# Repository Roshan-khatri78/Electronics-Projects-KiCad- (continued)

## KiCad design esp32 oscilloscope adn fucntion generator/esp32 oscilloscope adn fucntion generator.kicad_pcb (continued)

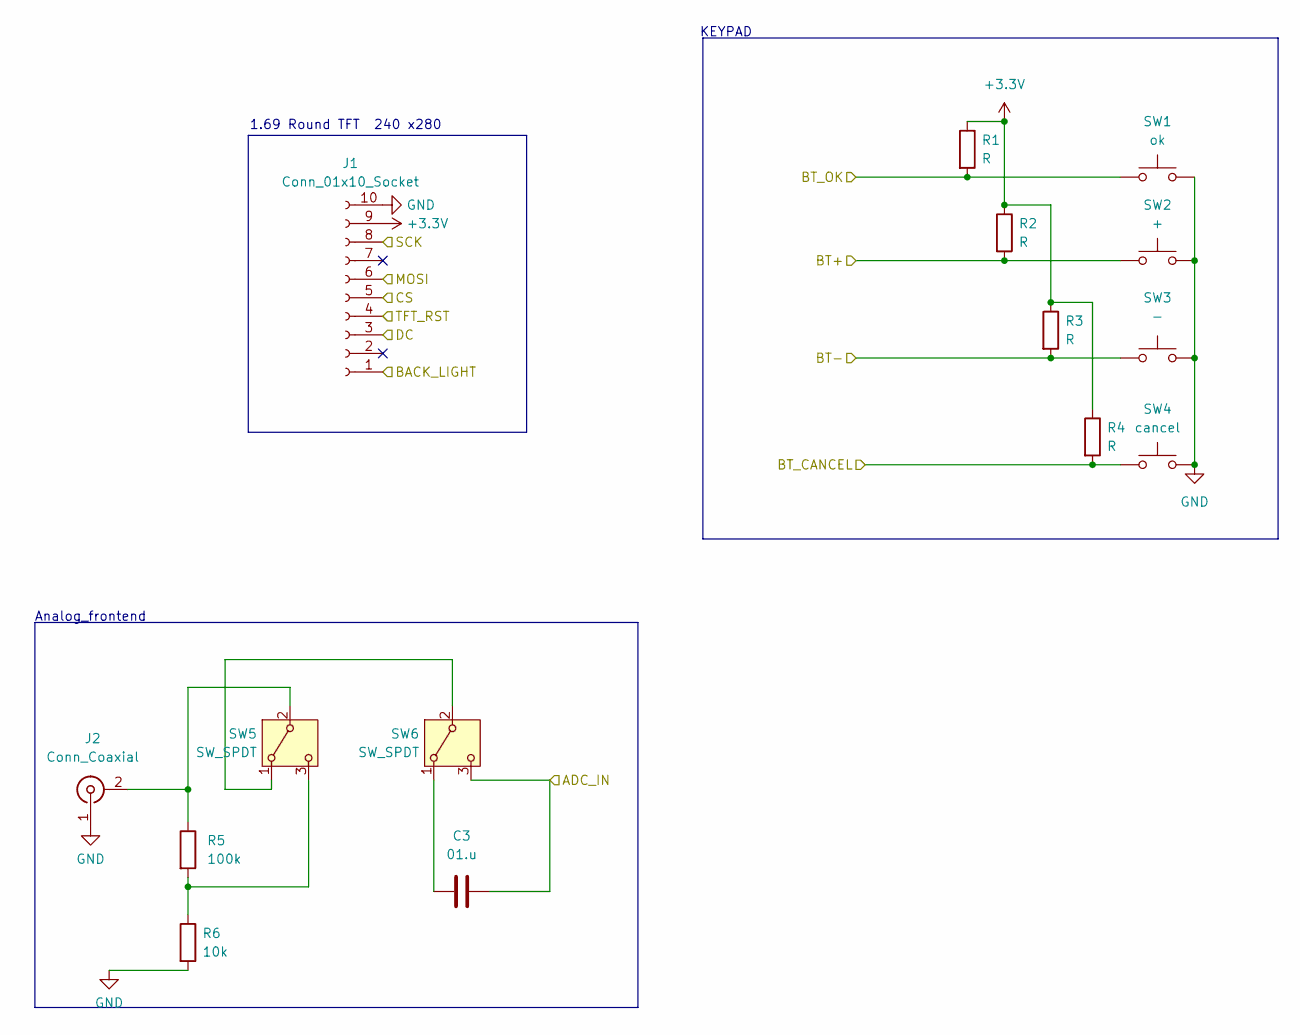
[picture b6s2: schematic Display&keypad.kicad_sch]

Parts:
C3: 01.u; C_1210_3225Metric
J1: Conn_01x10_Socket; PinSocket_1x10_P2.00mm_Vertical
J2: Conn_Coaxial; BNC_TEConnectivity_1478035_Horizontal
R1, R2, R3, R4: R; R_1210_3225Metric
R5: 100k; R_1210_3225Metric
R6: 10k; R_1210_3225Metric
SW1: ok; SW_PUSH_6mm
SW2: +; SW_PUSH_6mm
SW3: -; SW_PUSH_6mm
SW4: cancel; SW_PUSH_6mm
SW5, SW6: SW_SPDT; SW_E-Switch_EG1271_SPDT

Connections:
+3.3V: J1.9, R1.1, R2.1, R3.1, R4.1; also elsewhere on the board
/ADC_IN: C3.2, SW6.3 (C); also elsewhere on the board
/BACKLIGHT: J1.1; also elsewhere on the board
/BT+: R1.2, SW1.1; also elsewhere on the board
/BT-: R3.2, SW3.1; also elsewhere on the board
/BT_CANCEL: R4.2, SW4.1; also elsewhere on the board
/BT_OK: R2.2, SW2.1; also elsewhere on the board
/CS: J1.5; also elsewhere on the board
/DC: J1.3; also elsewhere on the board
/MOSI: J1.6; also elsewhere on the board
/SCK: J1.8; also elsewhere on the board
/TFT_RST: J1.4; also elsewhere on the board
GND: J1.10, J2.1 (In), R6.2, SW1.2, SW2.2, SW3.2, SW4.2; also elsewhere on the board
unnamed: J2.2 (Ext), R5.1, SW5.2 (B)
unnamed: SW5.1 (A), SW6.2 (B)
unnamed: R5.2, R6.1, SW5.3 (C)
unnamed: C3.1, SW6.1 (A)

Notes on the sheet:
Analog_frontend
1.69 Round TFT 240 x280
KEYPAD

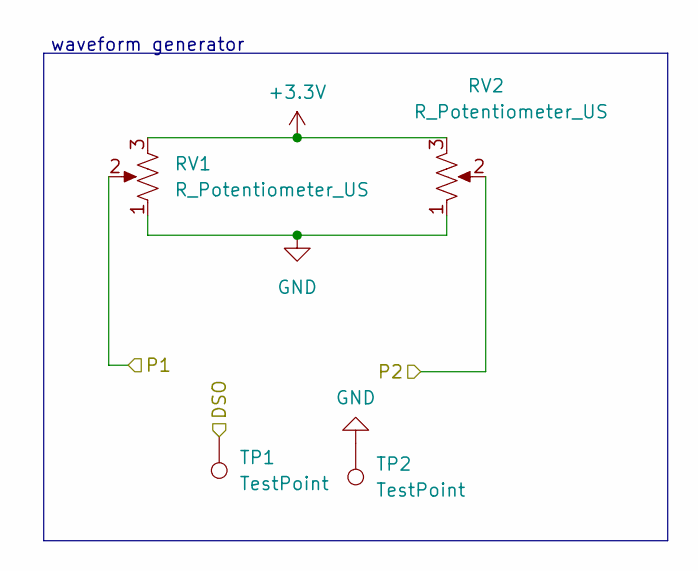
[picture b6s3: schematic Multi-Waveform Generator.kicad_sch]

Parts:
RV1, RV2: R_Potentiometer_US; Potentiometer_Alpha_RD901F-40-00D_Single_Vertical_CircularH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
TP1, TP2: TestPoint; TestPoint_Pad_2.0x2.0mm

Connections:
+3.3V: RV1.3, RV2.3; also elsewhere on the board
/DSO: TP1.1 (1_1); also elsewhere on the board
/P1: RV1.2; also elsewhere on the board
/P2: RV2.2; also elsewhere on the board
GND: RV1.1, RV2.1, TP2.1 (1_1); also elsewhere on the board

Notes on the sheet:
waveform generator

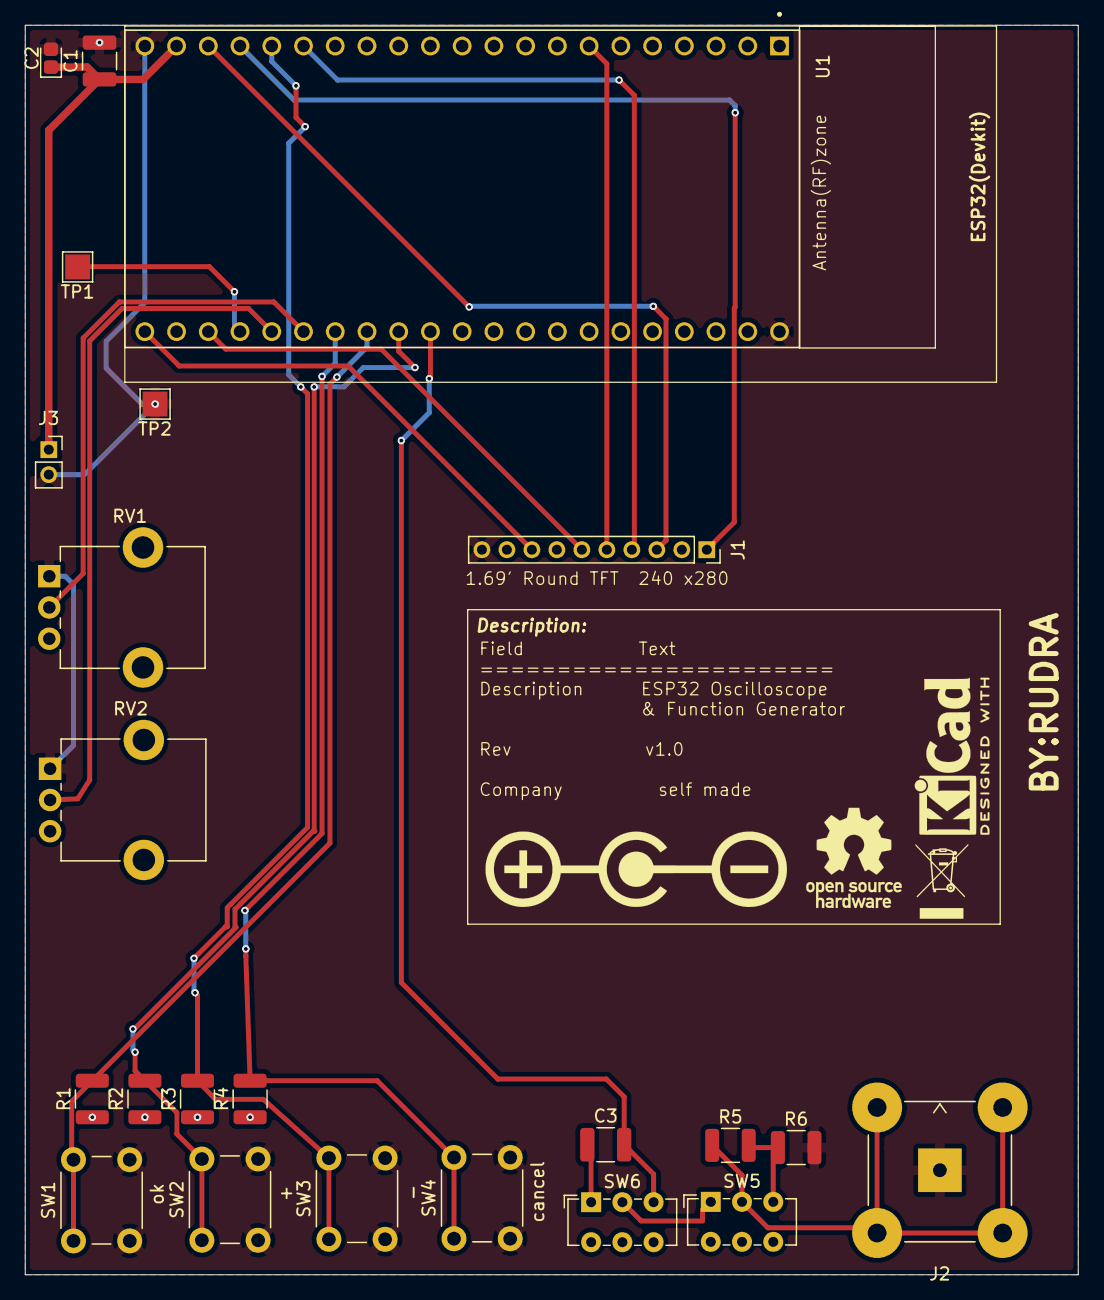
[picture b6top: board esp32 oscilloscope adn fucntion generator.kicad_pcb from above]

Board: 4 copper layers, 84.3 x 100.0 mm, 23 parts (0 on the bottom side), 21 nets.

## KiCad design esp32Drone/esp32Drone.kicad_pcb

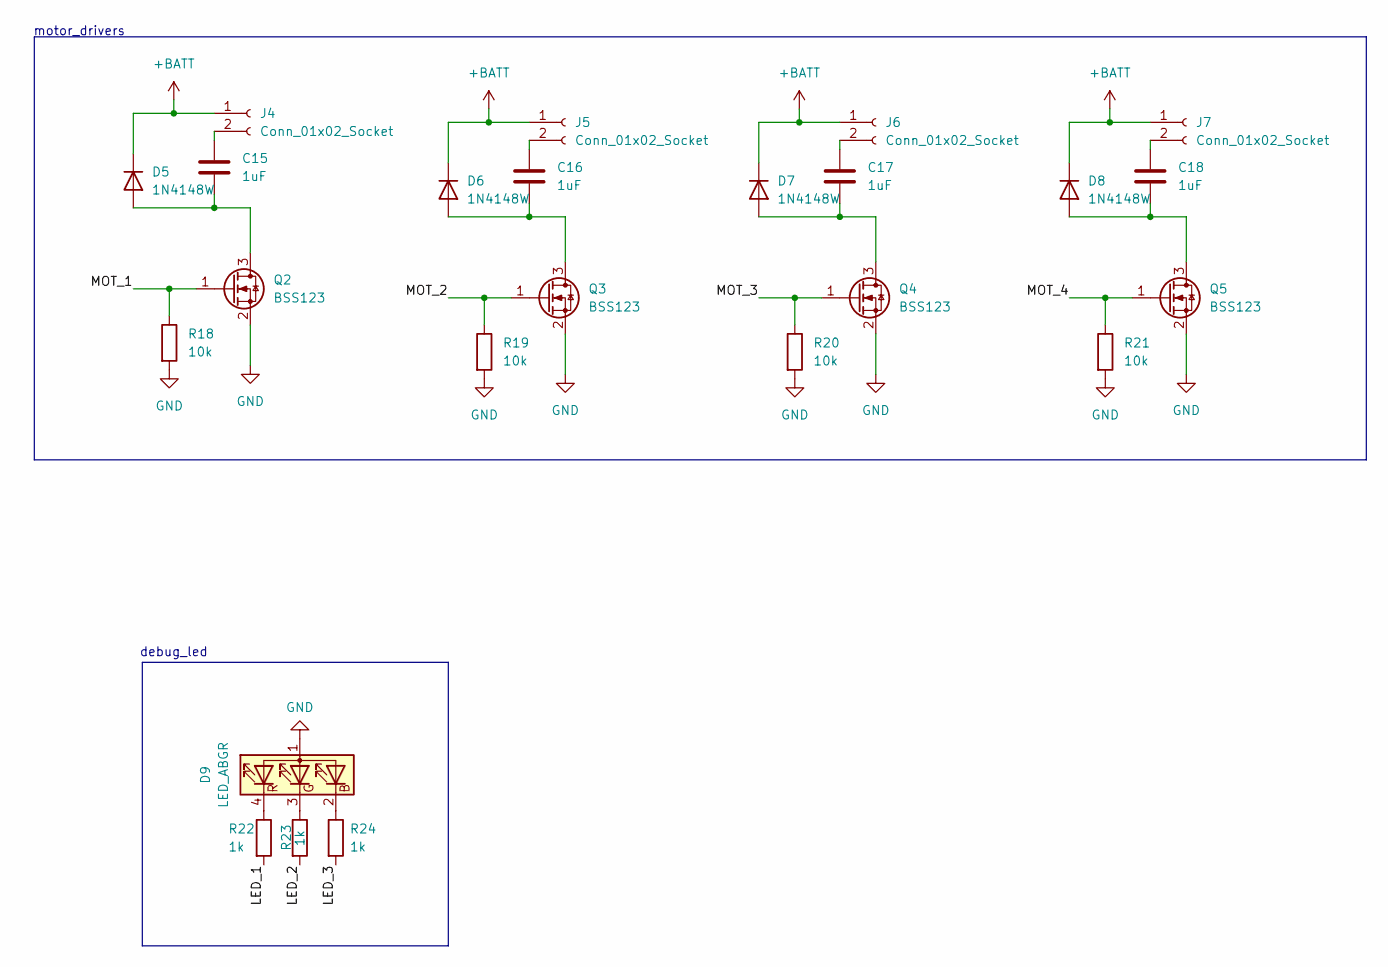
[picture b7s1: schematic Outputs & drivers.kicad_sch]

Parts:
C15, C16, C17, C18: 1uF; C_0805_2012Metric
D5, D6, D7, D8: 1N4148W; D_SOD-123
D9: LED_ABGR; LED_RGB_1210
J4, J5, J6, J7: Conn_01x02_Socket; PinSocket_1x02_P2.00mm_Vertical
Q2, Q3, Q4, Q5: BSS123; SOT-23
R18, R19, R20, R21: 10k; R_0805_2012Metric
R22, R23, R24: 1k; R_0805_2012Metric

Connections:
+BATT: D5.1 (K), D6.1 (K), D7.1 (K), D8.1 (K), J4.1, J5.1, J6.1, J7.1; also elsewhere on the board
/Outputs & drivers/LED_1: R22.2
/Outputs & drivers/LED_2: R23.2
/Outputs & drivers/LED_3: R24.2
/Outputs & drivers/MOT_1: Q2.1 (G), R18.1
/Outputs & drivers/MOT_2: Q3.1 (G), R19.1
/Outputs & drivers/MOT_3: Q4.1 (G), R20.1
/Outputs & drivers/MOT_4: Q5.1 (G), R21.1
GND: D9.1 (A), Q2.2 (S), Q3.2 (S), Q4.2 (S), Q5.2 (S), R18.2, R19.2, R20.2, R21.2; also elsewhere on the board
unnamed: C15.2, D5.2 (A), Q2.3 (D)
unnamed: C16.2, D6.2 (A), Q3.3 (D)
unnamed: C17.2, D7.2 (A), Q4.3 (D)
unnamed: C18.2, D8.2 (A), Q5.3 (D)
unnamed: D9.2 (BK), R24.1
unnamed: D9.3 (GK), R23.1
unnamed: D9.4 (RK), R22.1
unnamed: C15.1, J4.2
unnamed: C16.1, J5.2
unnamed: C17.1, J6.2
unnamed: C18.1, J7.2

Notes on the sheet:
motor_drivers
debug_led

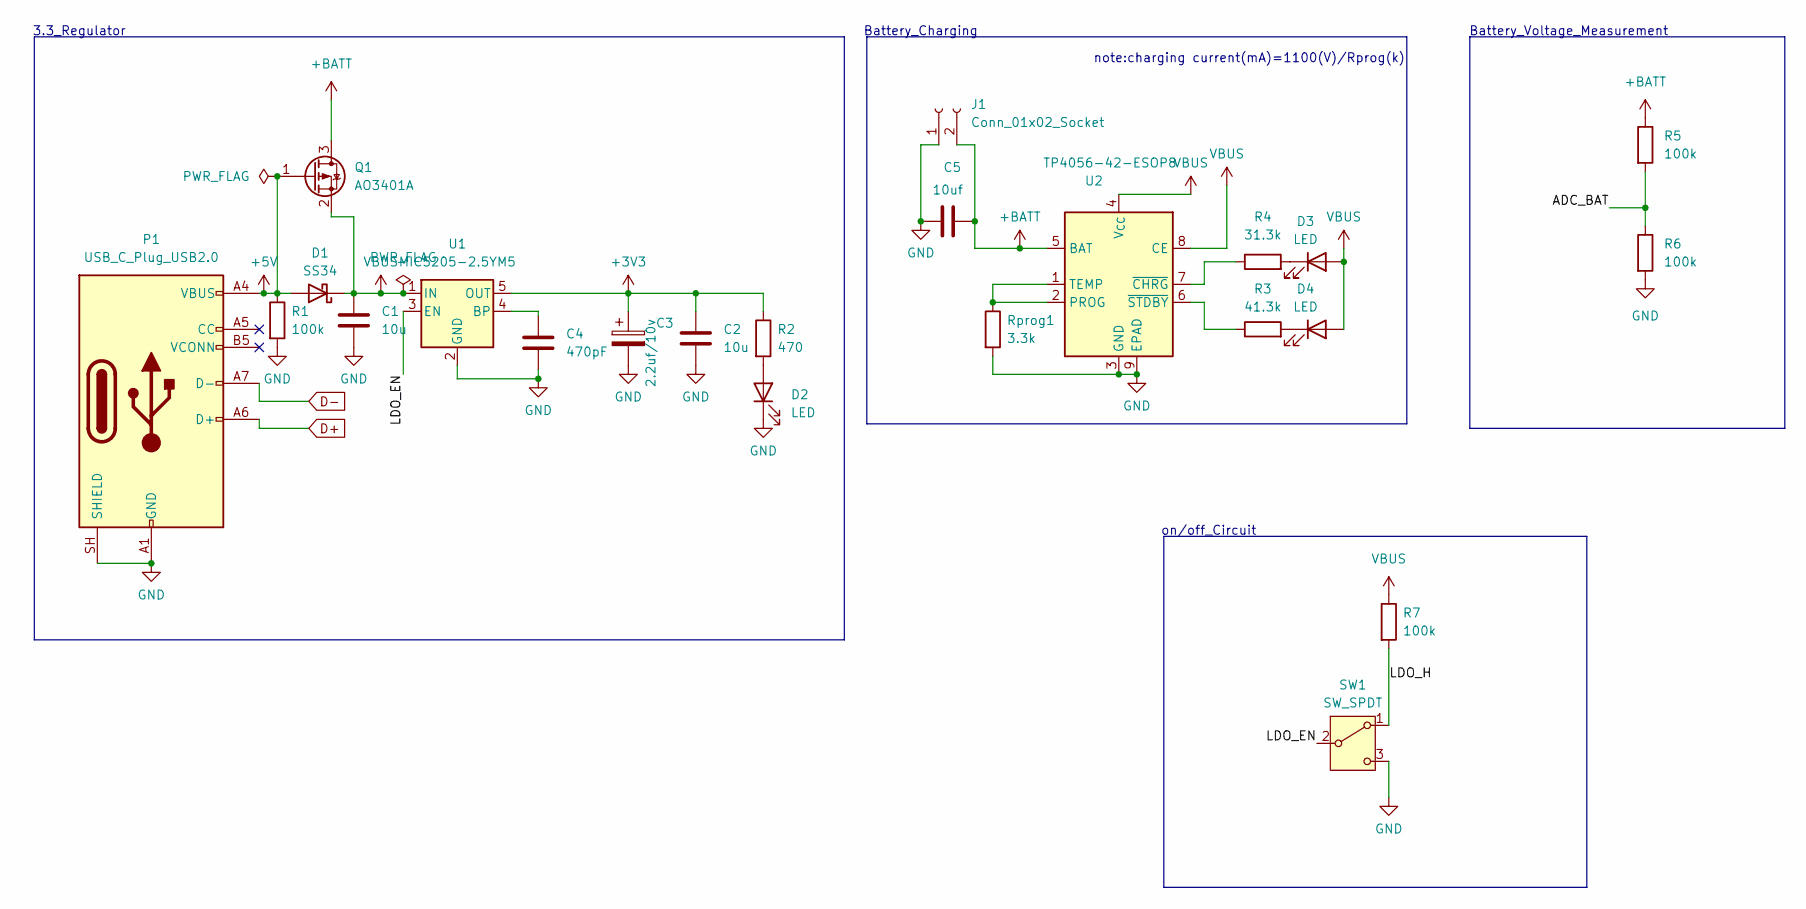
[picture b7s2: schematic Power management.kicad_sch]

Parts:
C1, C2: 10u; C_0805_2012Metric
C3: 2.2uf/10v; CP_EIA-1608-08_AVX-J_HandSolder
C4: 470pF; C_0805_2012Metric
C5: 10uf; C_0805_2012Metric
D1: SS34; D_SMA
D2, D3, D4: LED; LED_0805_2012Metric
J1: Conn_01x02_Socket; TerminalBlock_MaiXu_MX126-5.0-02P_1x02_P5.00mm
P1: USB_C_Plug_USB2.0; USB_C_Receptacle_HRO_TYPE-C-31-M-12
Q1: AO3401A; SOT-23
R1, R5, R6, R7: 100k; R_0805_2012Metric
R2: 470; R_0805_2012Metric
R3: 41.3k; R_0805_2012Metric
R4: 31.3k; R_0805_2012Metric
Rprog1: 3.3k; R_0805_2012Metric
SW1: SW_SPDT; SW_SPDT_PCM12
U1: MIC5205-2.5YM5; SOT-23-5
U2: TP4056-42-ESOP8; SOIC-8-1EP_3.9x4.9mm_P1.27mm_EP2.41x3.3mm_ThermalVias

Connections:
+3V3: C2.1, C3.1, R2.1, U1.5 (OUT); also elsewhere on the board
+5V: D1.2 (A), P1.A4 (VBUS), P1.A9 (VBUS), P1.B4 (VBUS), P1.B9 (VBUS), Q1.1 (G), R1.1; also elsewhere on the board
+BATT: C5.2, J1.2, Q1.3 (D), R5.1, U2.5 (BAT); also elsewhere on the board
/Power management/ADC_BAT: R5.2, R6.1
/Power management/LDO_EN: SW1.2 (B), U1.3 (EN)
/Power management/LDO_H: R7.2, SW1.1 (A)
GND: C1.2, C2.2, C3.2, C4.2, C5.1, D2.1 (K), J1.1, P1.A1 (GND), P1.A12 (GND), P1.B1 (GND), P1.B12 (GND), P1.SH (SHIELD), R1.2, R6.2, Rprog1.2, SW1.3 (C), U1.2 (GND), U2.3 (GND), U2.9 (EPAD); also elsewhere on the board
unnamed: D2.2 (A), R2.2
unnamed: D3.1 (K), R4.2
unnamed: D4.1 (K), R3.2
unnamed: C4.1, U1.4 (BP)
unnamed: Rprog1.1, U2.1 (TEMP), U2.2 (PROG)
unnamed: R4.1, U2.7 (~CHRG)
unnamed: R3.1, U2.6 (~STDBY)
VBUS: C1.1, D1.1 (K), D3.2 (A), D4.2 (A), Q1.2 (S), R7.1, U1.1 (IN), U2.4 (V_{CC}), U2.8 (CE); also elsewhere on the board

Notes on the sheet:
Battery_Voltage_Measurement
note:charging current(mA)=1100(V)/Rprog(k)
on/off_Circuit
Battery_Charging
3.3_Regulator

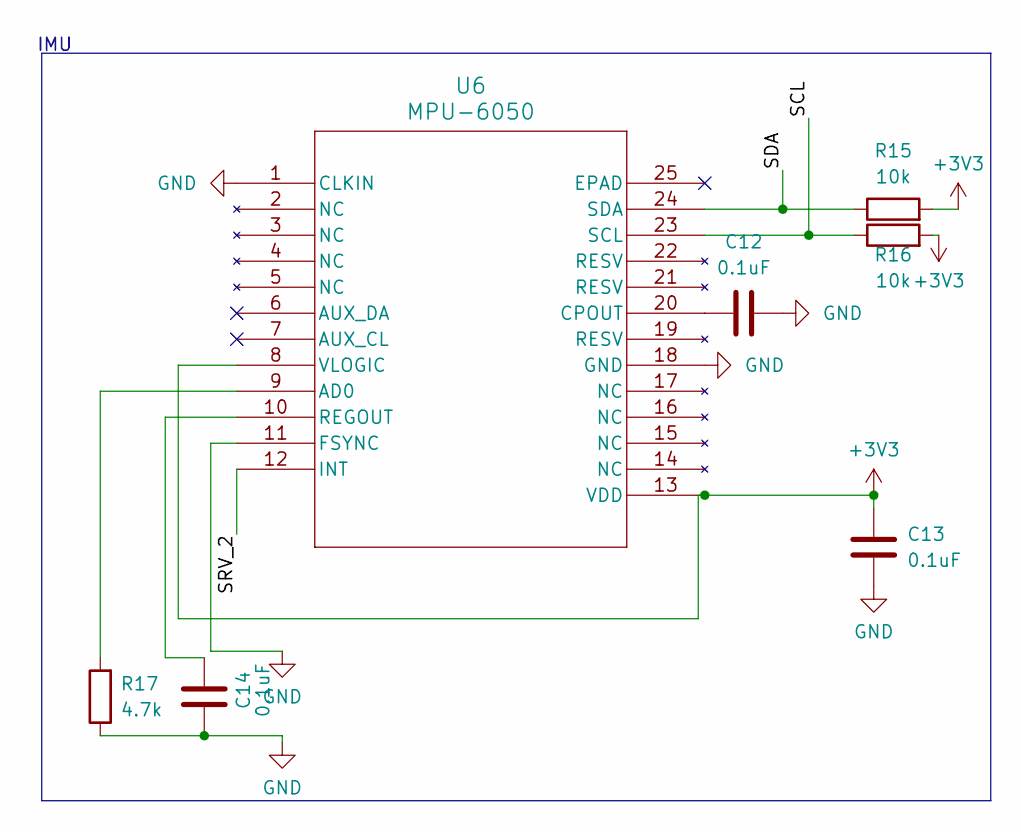
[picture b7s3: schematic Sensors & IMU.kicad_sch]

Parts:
C12, C13, C14: 0.1uF; C_0805_2012Metric
R15, R16: 10k; R_0805_2012Metric
R17: 4.7k; R_0805_2012Metric
U6: MPU-6050; QFN24_4X4X0P9-0P5_TDK-M

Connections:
+3V3: C13.1, R15.2, R16.2, U6.8 (VLOGIC), U6.13 (VDD); also elsewhere on the board
/Sensors & IMU/SCL: R16.1, U6.23 (SCL); also elsewhere on the board
/Sensors & IMU/SDA: R15.1, U6.24 (SDA); also elsewhere on the board
GND: C12.1, C13.2, C14.2, R17.1, U6.1 (CLKIN), U6.11 (FSYNC), U6.18 (GND); also elsewhere on the board
unnamed 70: R17.2, U6.9 (AD0); also elsewhere on the board
unnamed 71: C12.2, U6.20 (CPOUT); also elsewhere on the board
unnamed 72: C14.1, U6.10 (REGOUT); also elsewhere on the board

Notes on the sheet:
IMU

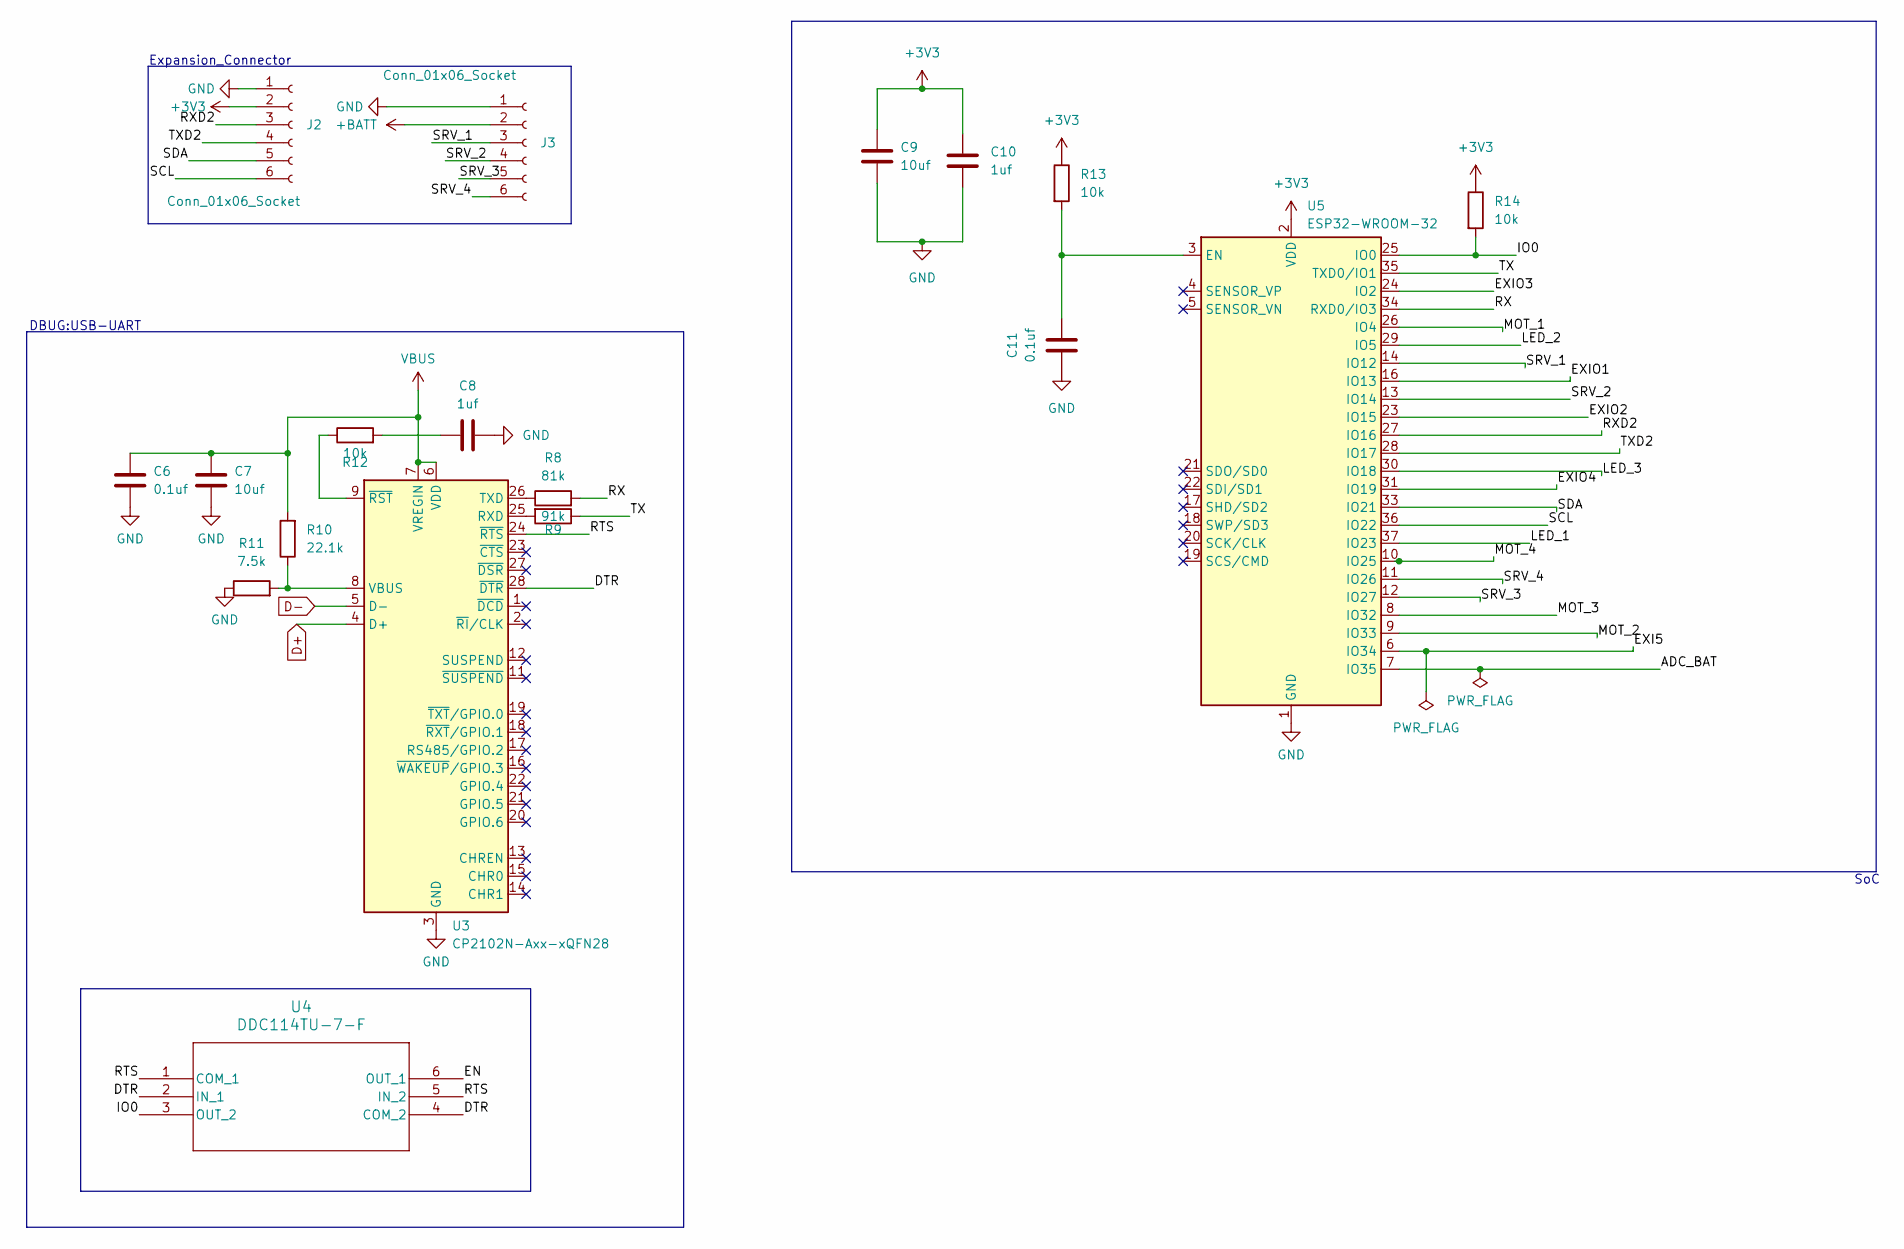
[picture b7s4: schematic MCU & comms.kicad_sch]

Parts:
C6, C11: 0.1uf; C_0805_2012Metric
C7, C9: 10uf; C_0805_2012Metric
C8, C10: 1uf; C_0805_2012Metric
J2, J3: Conn_01x06_Socket; PinSocket_1x06_P2.00mm_Vertical
R8: 81k; R_0805_2012Metric
R9: 91k; R_0805_2012Metric
R10: 22.1k; R_0805_2012Metric
R11: 7.5k; R_0805_2012Metric
R12, R13, R14: 10k; R_0805_2012Metric
U3: CP2102N-Axx-xQFN28; QFN-28-1EP_5x5mm_P0.5mm_EP3.35x3.35mm
U4: DDC114TU-7-F; SOT_363_DIO-M
U5: ESP32-WROOM-32

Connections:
+3V3: C9.2, C10.2, J2.2, R13.1, R14.1, U5.2 (VDD); also elsewhere on the board
+BATT: J3.2; also elsewhere on the board
/MCU & comms/ADC_BAT: U5.7 (IO35)
/MCU & comms/DTR: U3.28 (~DTR), U4.2 (IN_1), U4.4 (COM_2)
/MCU & comms/EN: U4.6 (OUT_1)
/MCU & comms/EXI5: U5.6 (IO34)
/MCU & comms/EXIO1: U5.16 (IO13)
/MCU & comms/EXIO2: U5.23 (IO15)
/MCU & comms/EXIO3: U5.24 (IO2)
/MCU & comms/EXIO4: U5.31 (IO19)
/MCU & comms/IO0: R14.2, U4.3 (OUT_2), U5.25 (IO0)
/MCU & comms/LED_1: U5.37 (IO23)
/MCU & comms/LED_2: U5.29 (IO5)
/MCU & comms/LED_3: U5.30 (IO18)
/MCU & comms/MOT_1: U5.26 (IO4)
/MCU & comms/MOT_2: U5.9 (IO33)
/MCU & comms/MOT_3: U5.8 (IO32)
/MCU & comms/MOT_4: U5.10 (IO25)
/MCU & comms/RTS: U3.24 (~RTS), U4.1 (COM_1), U4.5 (IN_2)
/MCU & comms/RX: R8.2, U5.34 (RXD0/IO3)
/MCU & comms/RXD2: J2.3, U5.27 (IO16)
/MCU & comms/SCL: J2.6, U5.36 (IO22)
/MCU & comms/SDA: J2.5, U5.33 (IO21)
/MCU & comms/SRV_1: J3.3, U5.14 (IO12)
/MCU & comms/SRV_2: J3.4, U5.13 (IO14)
/MCU & comms/SRV_3: J3.5, U5.12 (IO27)
/MCU & comms/SRV_4: J3.6, U5.11 (IO26)
/MCU & comms/TX: R9.1, U5.35 (TXD0/IO1)
/MCU & comms/TXD2: J2.4, U5.28 (IO17)
D+: U3.4 (D+); also elsewhere on the board
D-: U3.5 (D-); also elsewhere on the board
GND: C6.2, C7.2, C8.2, C9.1, C10.1, C11.1, J2.1, J3.1, R11.1, U3.3 (GND), U3.29 (GND), U5.1 (GND), U5.15 (GND), U5.38 (GND), U5.39 (GND); also elsewhere on the board
unnamed: C8.1, R12.2
unnamed: R9.2, U3.25 (RXD)
unnamed: R8.1, U3.26 (TXD)
unnamed: R10.1, R11.2, U3.8 (VBUS)
unnamed: R12.1, U3.9 (~RST)
unnamed: C11.2, R13.2, U5.3 (EN)
VBUS: C6.1, C7.1, R10.2, U3.6 (VDD), U3.7 (VREGIN); also elsewhere on the board

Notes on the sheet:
SoC
DBUG:USB-UART
Expansion_Connector

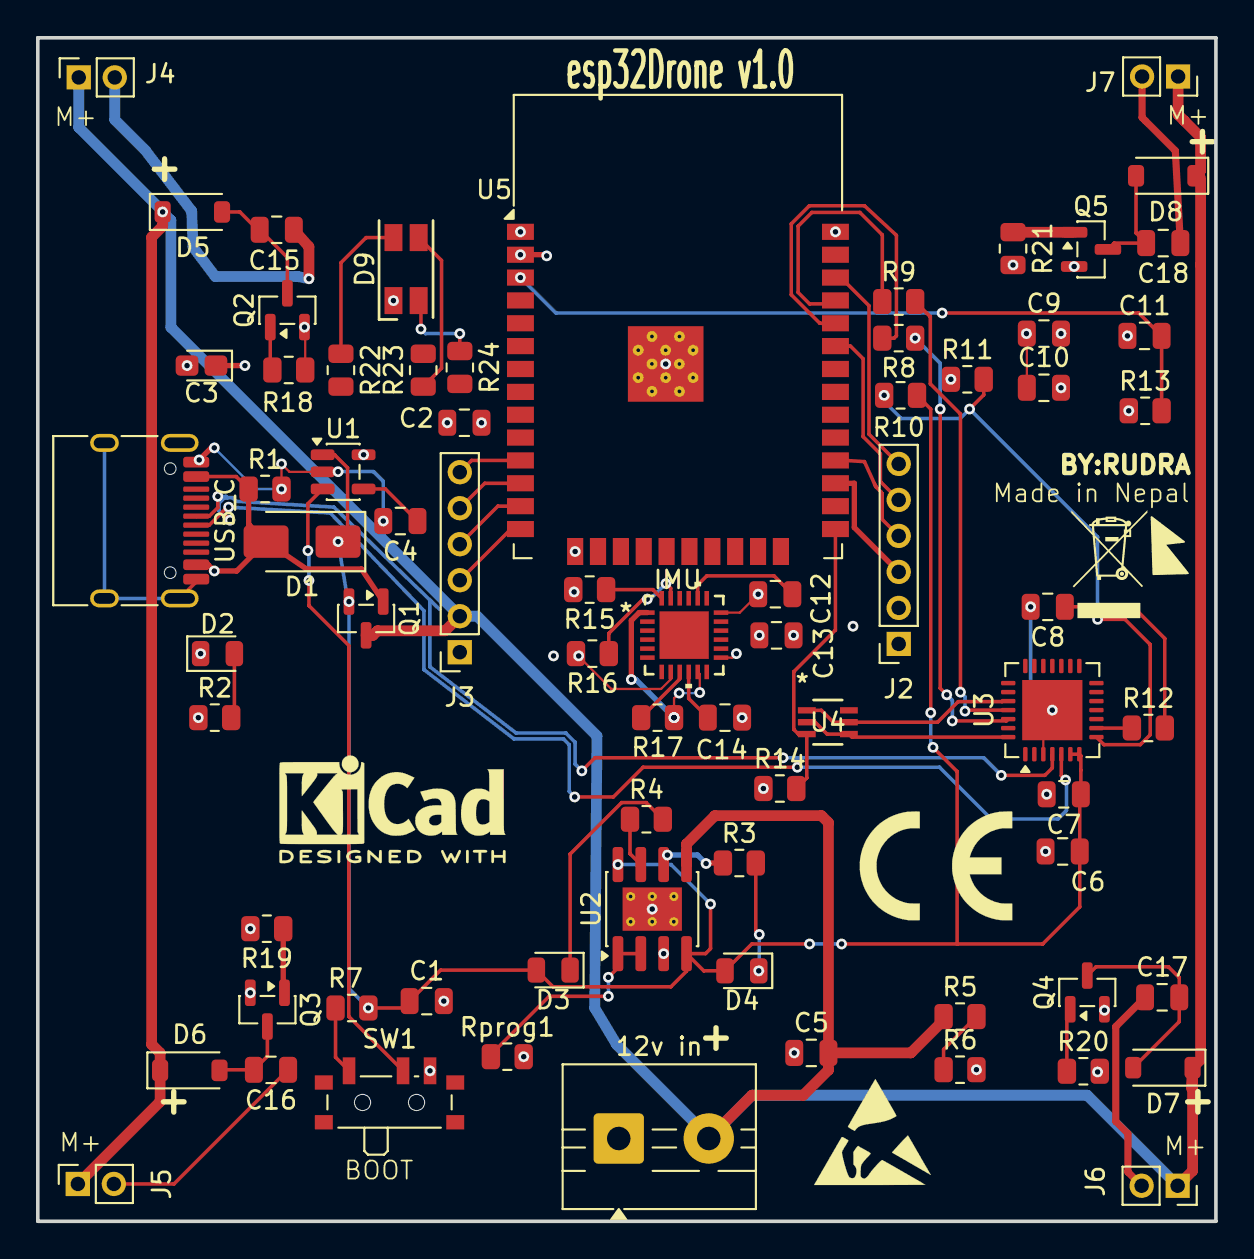
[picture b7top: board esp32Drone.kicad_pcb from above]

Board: 4 copper layers, 65.5 x 65.8 mm, 72 parts (0 on the bottom side), 56 nets.

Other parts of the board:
12v in: Conn_01x02_Socket; TerminalBlock_MaiXu_MX126-5.0-02P_1x02_P5.00mm
IMU: MPU-6050; QFN24_4X4X0P9-0P5_TDK-M
USB_C: USB_C_Plug_USB2.0; USB_C_Receptacle_HRO_TYPE-C-31-M-12

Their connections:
+3V3: IMU.8 (VLOGIC), IMU.13 (VDD); also elsewhere on the board
+5V: USB_C.A4 (VBUS), USB_C.A9 (VBUS), USB_C.B4 (VBUS), USB_C.B9 (VBUS); also elsewhere on the board
+BATT: 12v in.2; also elsewhere on the board
/Sensors & IMU/SCL: IMU.23 (SCL); also elsewhere on the board
/Sensors & IMU/SDA: IMU.24 (SDA); also elsewhere on the board
D+: USB_C.A6 (D+); also elsewhere on the board
D-: USB_C.A7 (D-); also elsewhere on the board
GND: 12v in.1, IMU.1 (CLKIN), IMU.11 (FSYNC), IMU.18 (GND), USB_C.A1 (GND), USB_C.A12 (GND), USB_C.B1 (GND), USB_C.B12 (GND), USB_C.SH (SHIELD); also elsewhere on the board
unnamed 70: IMU.9 (AD0); also elsewhere on the board
unnamed 71: IMU.20 (CPOUT); also elsewhere on the board
unnamed 72: IMU.10 (REGOUT); also elsewhere on the board

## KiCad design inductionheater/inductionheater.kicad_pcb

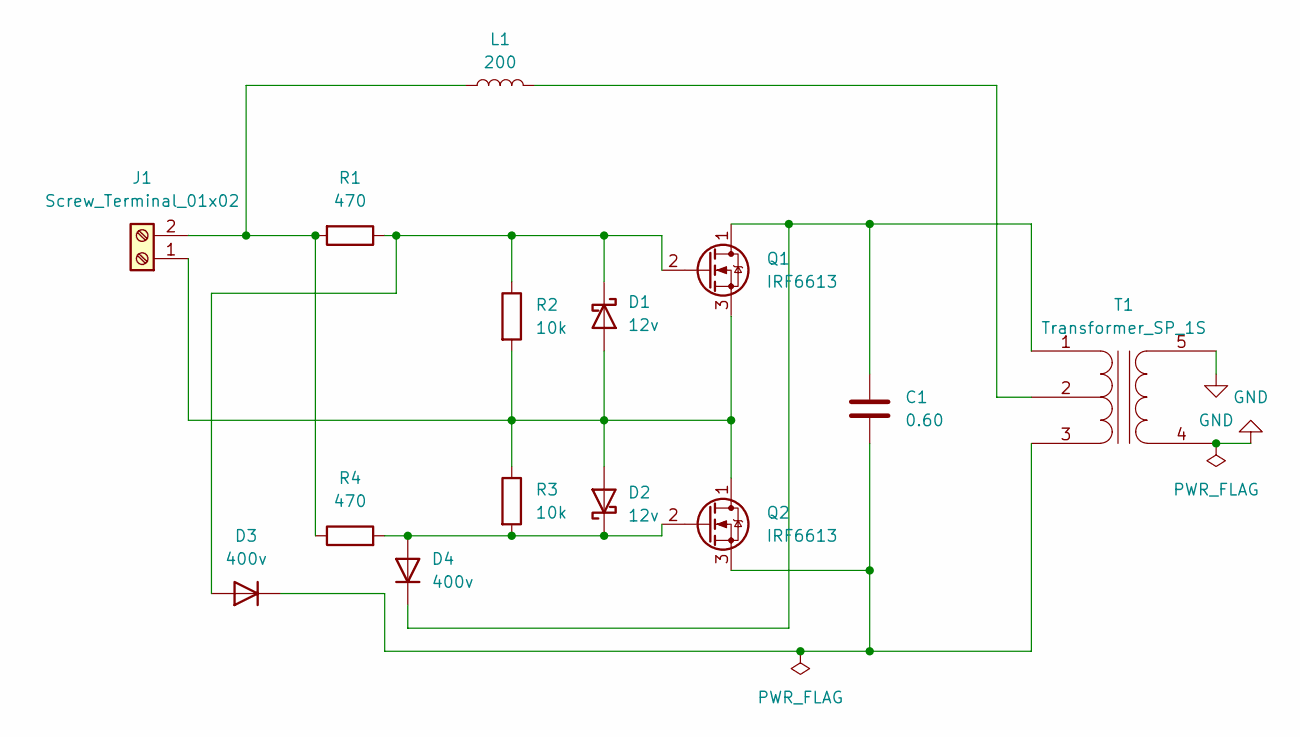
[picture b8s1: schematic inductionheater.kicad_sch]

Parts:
C1: 0.60; CP_Axial_L10.0mm_D4.5mm_P15.00mm_Horizontal
D1: 12v; CP_Axial_L10.0mm_D4.5mm_P15.00mm_Horizontal
D2: 12v; D_A-405_P7.62mm_Horizontal
D3: 400v; D_A-405_P7.62mm_Horizontal
D4: 400v; D_SOD-523
J1: Screw_Terminal_01x02; TerminalBlock_Phoenix_MKDS-1,5-2-5.08_1x02_P5.08mm_Horizont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
L1: 200; L_Axial_L5.0mm_D3.6mm_P10.00mm_Horizontal_Murata_BL01RN1A2A2
Q1, Q2: IRF6613; DirectFET_MT
R1, R4: 470; R_Axial_DIN0204_L3.6mm_D1.6mm_P1.90mm_Vertical
R2, R3: 10k; R_Axial_DIN0204_L3.6mm_D1.6mm_P1.90mm_Vertical
T1: Transformer_SP_1S; Transformer_NF_ETAL_1-1_P1200

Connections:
GND: T1.4 (S1), T1.5 (S2)
unnamed: D1.2 (A), D2.2 (A), J1.1, Q1.3 (S), Q2.1 (D), R2.2, R3.1
unnamed: D1.1 (K), D3.2 (A), Q1.2 (G), R1.1, R2.1
unnamed: D2.1 (K), D4.2 (A), Q2.2 (G), R3.2, R4.2
unnamed: C1.2, D3.1 (K), Q2.3 (S), T1.3 (PR2)
unnamed: C1.1, D4.1 (K), Q1.1 (D), T1.1 (PR1)
unnamed: J1.2, L1.1, R1.2, R4.1
unnamed: L1.2, T1.2 (PM)

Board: 2 copper layers, 14 parts (0 on the bottom side), 8 nets, no tracks yet.
